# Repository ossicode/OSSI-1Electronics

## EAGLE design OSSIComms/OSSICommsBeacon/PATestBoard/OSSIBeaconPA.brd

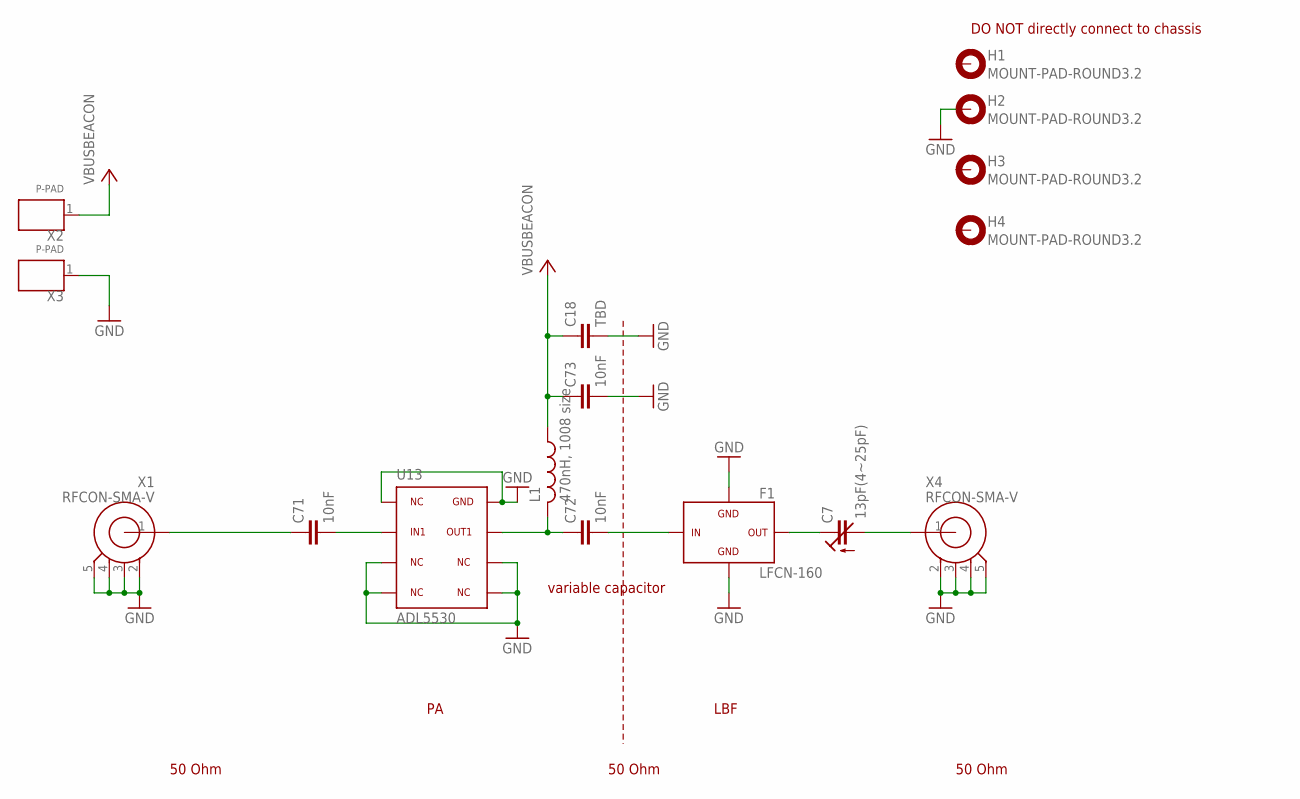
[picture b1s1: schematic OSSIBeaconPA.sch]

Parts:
C7: 13pF(4~25pF); TZB4Z250BA10R00
C18: TBD; C0603(1608)
C71, C72, C73: 10nF; C0603(1608)
F1: LFCN-160; LFCN
H1, H2, H3, H4: MOUNT-PAD-ROUND3.2; 3.2-PAD-ROUND
L1: 470nH, 1008 size; L1008(2520)
U13: ADL5530; LFCSP8_CP
X1, X4: RFCON-SMA-V; SMA-V
X2, X3: P-PAD

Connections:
GND: C18.2, C73.2, F1.2, F1.4, H2.B3,2, U13.1, U13.3, U13.4, U13.5, U13.6, U13.8, X1.2, X1.3, X1.4, X1.5, X3.1, X4.2, X4.3, X4.4, X4.5
unnamed: C71.1, X1.1
unnamed: C7.+ (E), F1.3
unnamed: C7.- (A), X4.1
unnamed: C72.2, F1.1
unnamed: C72.1, L1.P$2 (2), U13.7
unnamed: C71.2, U13.2
VBUSBEACON: C18.1, C73.1, L1.P$1 (1), X2.1

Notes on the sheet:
50 Ohm
LBF
variable capacitor
DO NOT directly connect to chassis

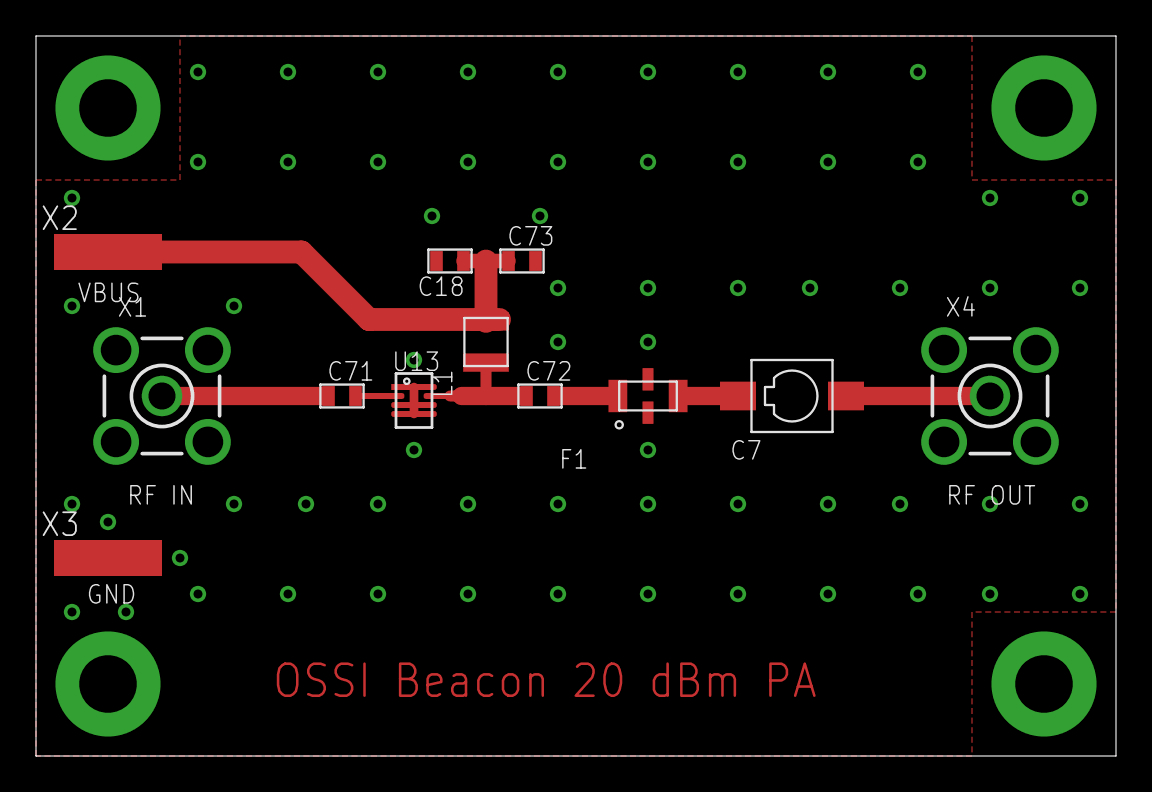
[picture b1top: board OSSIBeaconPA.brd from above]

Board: 2 copper layers, 60.0 x 40.0 mm, 16 parts (0 on the bottom side), 8 nets.

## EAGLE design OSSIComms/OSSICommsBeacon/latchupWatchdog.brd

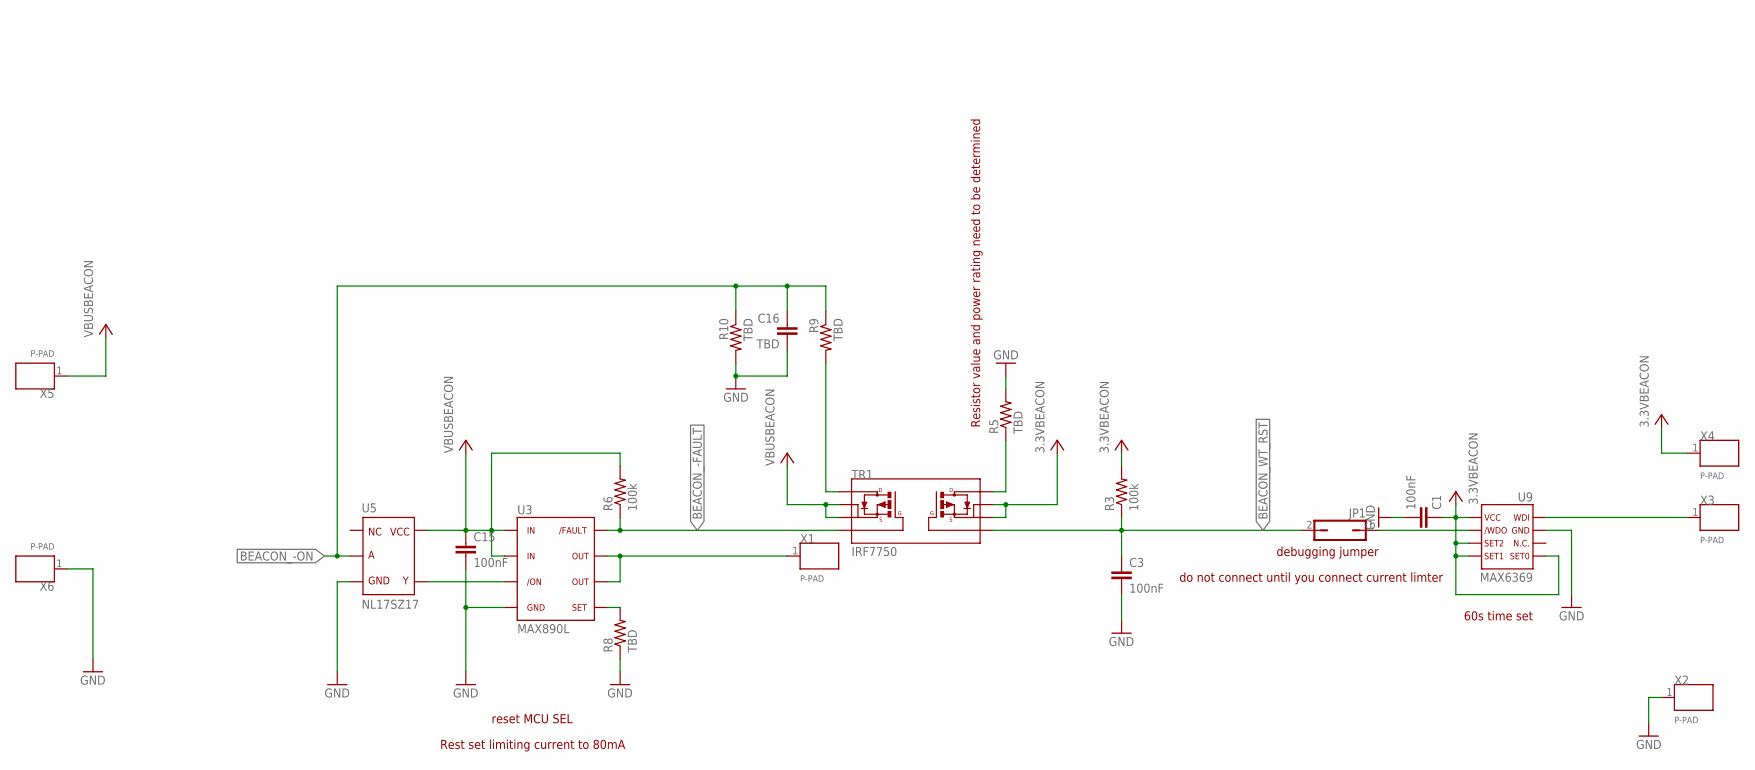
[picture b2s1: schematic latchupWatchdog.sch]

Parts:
C1, C3, C15: 100nF; C0603(1608)
C16: TBD; C0603(1608)
JP1: JP1Q; JP1
R3, R6: 100k; R0603(1608)
R5: TBD; R0805(2012)
R8, R9, R10: TBD; R0603(1608)
TR1: IRF7750; TSSOP-8
U3: MAX890L; SO8
U5: NL17SZ17; SOT-553
U9: MAX6369; SOT23-8
X1, X2, X3, X4, X5, X6: P-PAD

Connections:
3.3VBEACON: C1.1, R3.2, TR1.6, TR1.7, U9.4, U9.5, U9.6, U9.8, X4.1
BEACON_-FAULT: R6.1, TR1.4, U3.8
BEACON_-ON: C16.1, R9.1, R10.1, U5.2
BEACON_WT_RST: C3.1, JP1.2, R3.1, TR1.5
GND: C1.2, C3.2, C15.2, C16.2, R5.2, R8.1, R10.2, U3.4, U5.3, U9.2, X2.1, X6.1
unnamed: JP1.1, U9.7
unnamed: U9.1, X3.1
unnamed: R5.1, TR1.8
unnamed: U3.6, U3.7, X1.1
unnamed: R8.2, U3.5
unnamed: U3.3, U5.4
unnamed: R9.2, TR1.1
VBUSBEACON: C15.1, R6.2, TR1.2, TR1.3, U3.1, U3.2, U5.5, X5.1

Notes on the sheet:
60s time set
Resistor value and power rating need to be determined
debugging jumper
do not connect until you connect current limter
reset MCU SEL
Rest set limiting current to 80mA

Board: 2 copper layers, 21 parts (0 on the bottom side), 13 nets, no tracks yet.

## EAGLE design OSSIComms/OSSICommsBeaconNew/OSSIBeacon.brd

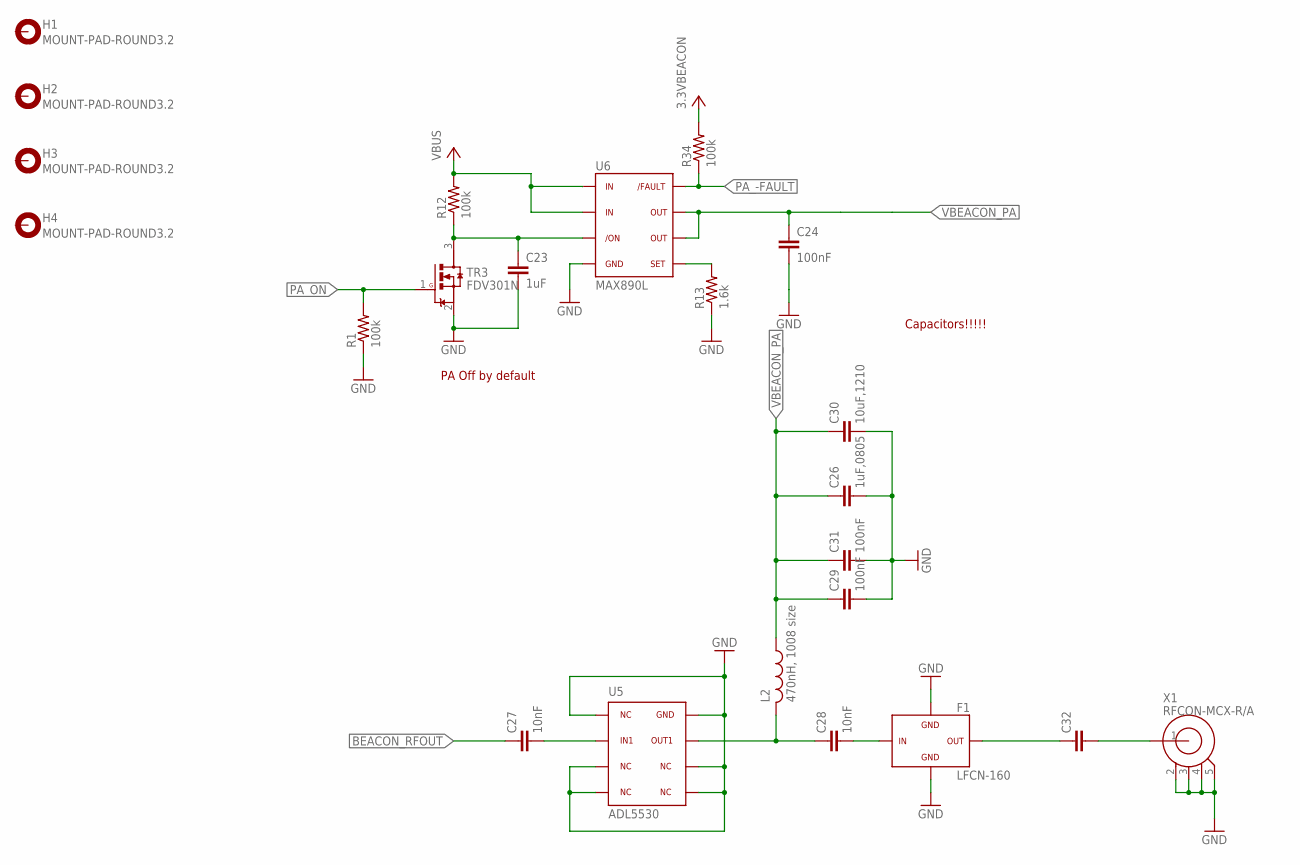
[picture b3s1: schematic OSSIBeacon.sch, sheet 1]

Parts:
C23: 1uF; C0603(1608)
C24, C29, C31: 100nF; C0603(1608)
C26: 1uF,0805; C0805(2012)
C27, C28: 10nF; C0603(1608)
C30: 10uF,1210; C1210-GCM32
C32: C0603(1608)
F1: LFCN-160; LFCN
H1, H2, H3, H4: MOUNT-PAD-ROUND3.2; 3.2-PAD-ROUND
L2: 470nH, 1008 size; L1008(2520)
R1, R12, R34: 100k; R0603(1608)
R13: 1.6k; R0603(1608)
TR3: FDV301N; SOT23
U5: ADL5530; LFCSP8_CP
U6: MAX890L; SO8
X1: RFCON-MCX-R/A; MCX-R/A

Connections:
3.3VBEACON: R34.2; also elsewhere on the board
BEACON_RFOUT: C27.1; also elsewhere on the board
GND: C23.2, C24.2, C26.2, C29.2, C30.P$2 (2), C31.2, F1.2, F1.4, R1.1, R13.1, TR3.2 (S), U5.1, U5.3, U5.4, U5.5, U5.6, U5.8, U6.4, X1.2, X1.3, X1.4, X1.5; also elsewhere on the board
unnamed: C23.1, R12.1, TR3.3 (D), U6.3
unnamed: R13.2, U6.5
unnamed: C27.2, U5.2
unnamed: C28.1, L2.P$2 (2), U5.7
unnamed: C28.2, F1.1
unnamed: C32.1, F1.3
unnamed: C32.2, X1.1
PA_-FAULT: R34.1, U6.8; also elsewhere on the board
PA_ON: R1.2, TR3.1 (G); also elsewhere on the board
VBEACON_PA: C24.1, C26.1, C29.1, C30.P$1 (1), C31.1, L2.P$1 (1), U6.6, U6.7
VBUS: R12.2, U6.1, U6.2; also elsewhere on the board

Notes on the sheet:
Capacitors!!!!!
PA Off by default

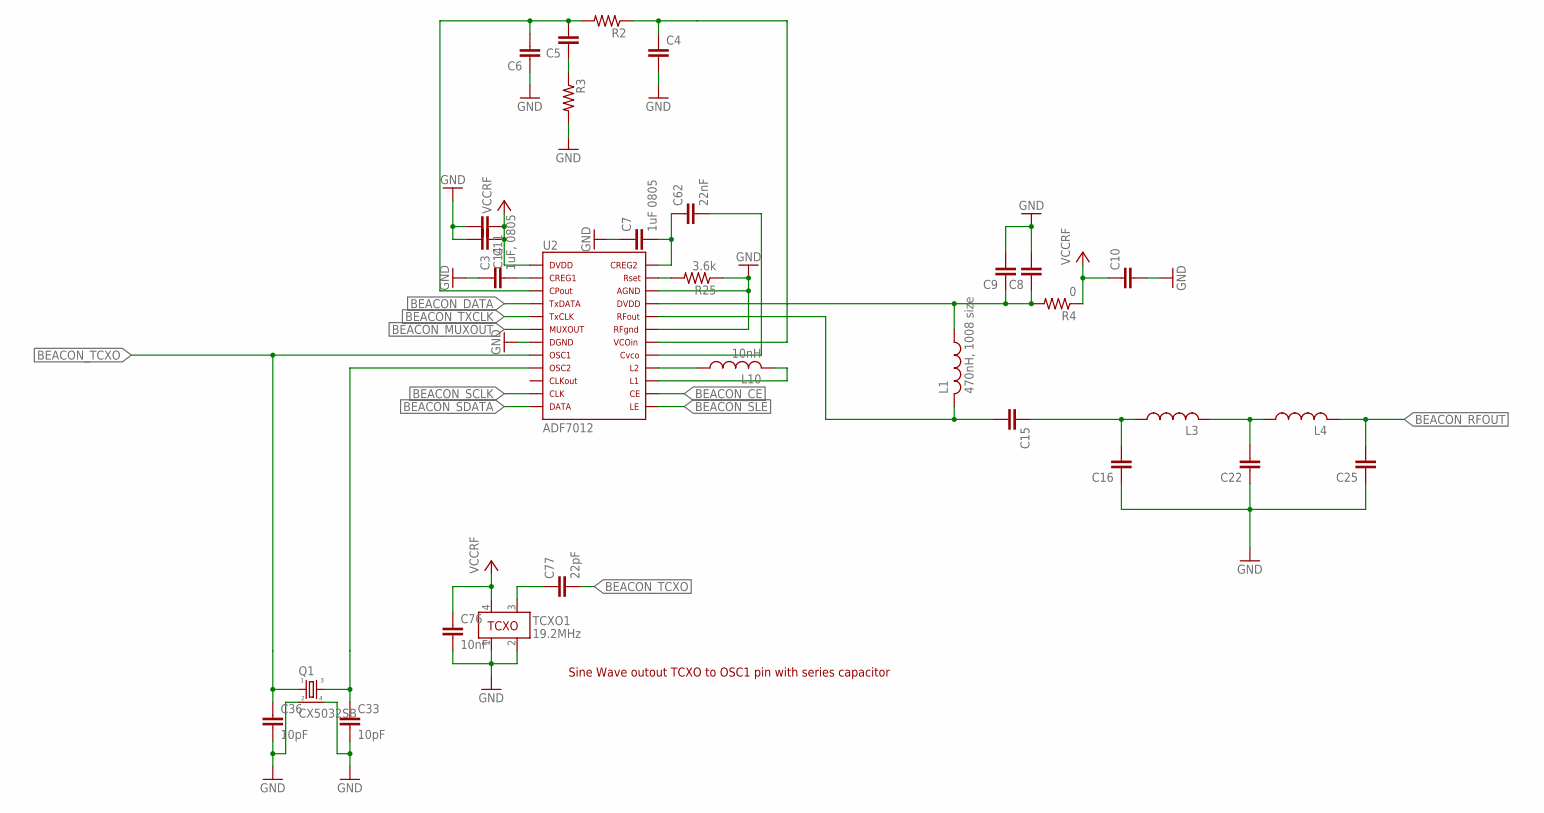
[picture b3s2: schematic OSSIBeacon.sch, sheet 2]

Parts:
C3: 1uF, 0805; C0805(2012)
C4, C5, C6, C8, C9, C10, C11, C14, C15, C16, C22, C25: C0603(1608)
C7: 1uF 0805; C0805(2012)
C33, C36: 10pF; C0603(1608)
C62: 22nF; C0603(1608)
C76: 10nF; C0603(1608)
C77: 22pF; C0603(1608)
L1: 470nH, 1008 size; L1008(2520)
L3, L4: L0603(1608)
L10: 10nH; L0603(1608)
Q1: CX5032SB; CX5032
R2, R3: R0603(1608)
R4: 0; R0603(1608)
R25: 3.6k; R0603(1608)
TCXO1: 19.2MHz; TCXO_M532
U2: ADF7012; TSSOP24

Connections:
BEACON_CE: U2.14 (CE); also elsewhere on the board
BEACON_DATA: U2.4 (TXDATA); also elsewhere on the board
BEACON_MUXOUT: U2.6 (MUXOUT); also elsewhere on the board
BEACON_RFOUT: C25.2, L4.2; also elsewhere on the board
BEACON_SCLK: U2.11 (CLK); also elsewhere on the board
BEACON_SDATA: U2.12 (DATA); also elsewhere on the board
BEACON_SLE: U2.13 (LE); also elsewhere on the board
BEACON_TCXO: C36.1, C77.2, Q1.1, U2.8 (OSC1)
BEACON_TXCLK: U2.5 (TXCLK); also elsewhere on the board
GND: C3.1, C4.2, C6.1, C7.1, C8.2, C9.2, C10.2, C11.2, C14.2, C16.1, C22.1, C25.1, C33.2, C36.2, C76.2, Q1.2, Q1.4, R3.2, R25.1, TCXO1.1, TCXO1.2, U2.7 (DGND), U2.19 (RFGND), U2.22 (AGND); also elsewhere on the board
unnamed: L10.1, U2.16 (L2)
unnamed: L10.2, U2.15 (L1)
unnamed: C7.2, C62.1, U2.24 (CREG2)
unnamed: C62.2, U2.17 (CVCO)
unnamed: R25.2, U2.23 (RSET)
unnamed: C5.1, R3.1
unnamed: C15.2, L1.P$2 (2), U2.20 (RFOUT)
unnamed: C4.1, R2.1, U2.18 (VCOIN)
unnamed: C3.2, U2.2 (CREG1)
unnamed: C5.2, C6.2, R2.2, U2.3 (CPOUT)
unnamed: C8.1, C9.1, L1.P$1 (1), R4.2, U2.21 (DVDD_2)
unnamed: C15.1, C16.2, L3.1
unnamed: C22.2, L3.2, L4.1
unnamed: C33.1, Q1.3, U2.9 (OSC2)
unnamed: C77.1, TCXO1.3
VCCRF: C10.1, C11.1, C14.1, C76.1, R4.1, TCXO1.4, U2.1 (DVDD_1); also elsewhere on the board

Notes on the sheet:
Sine Wave outout TCXO to OSC1 pin with series capacitor

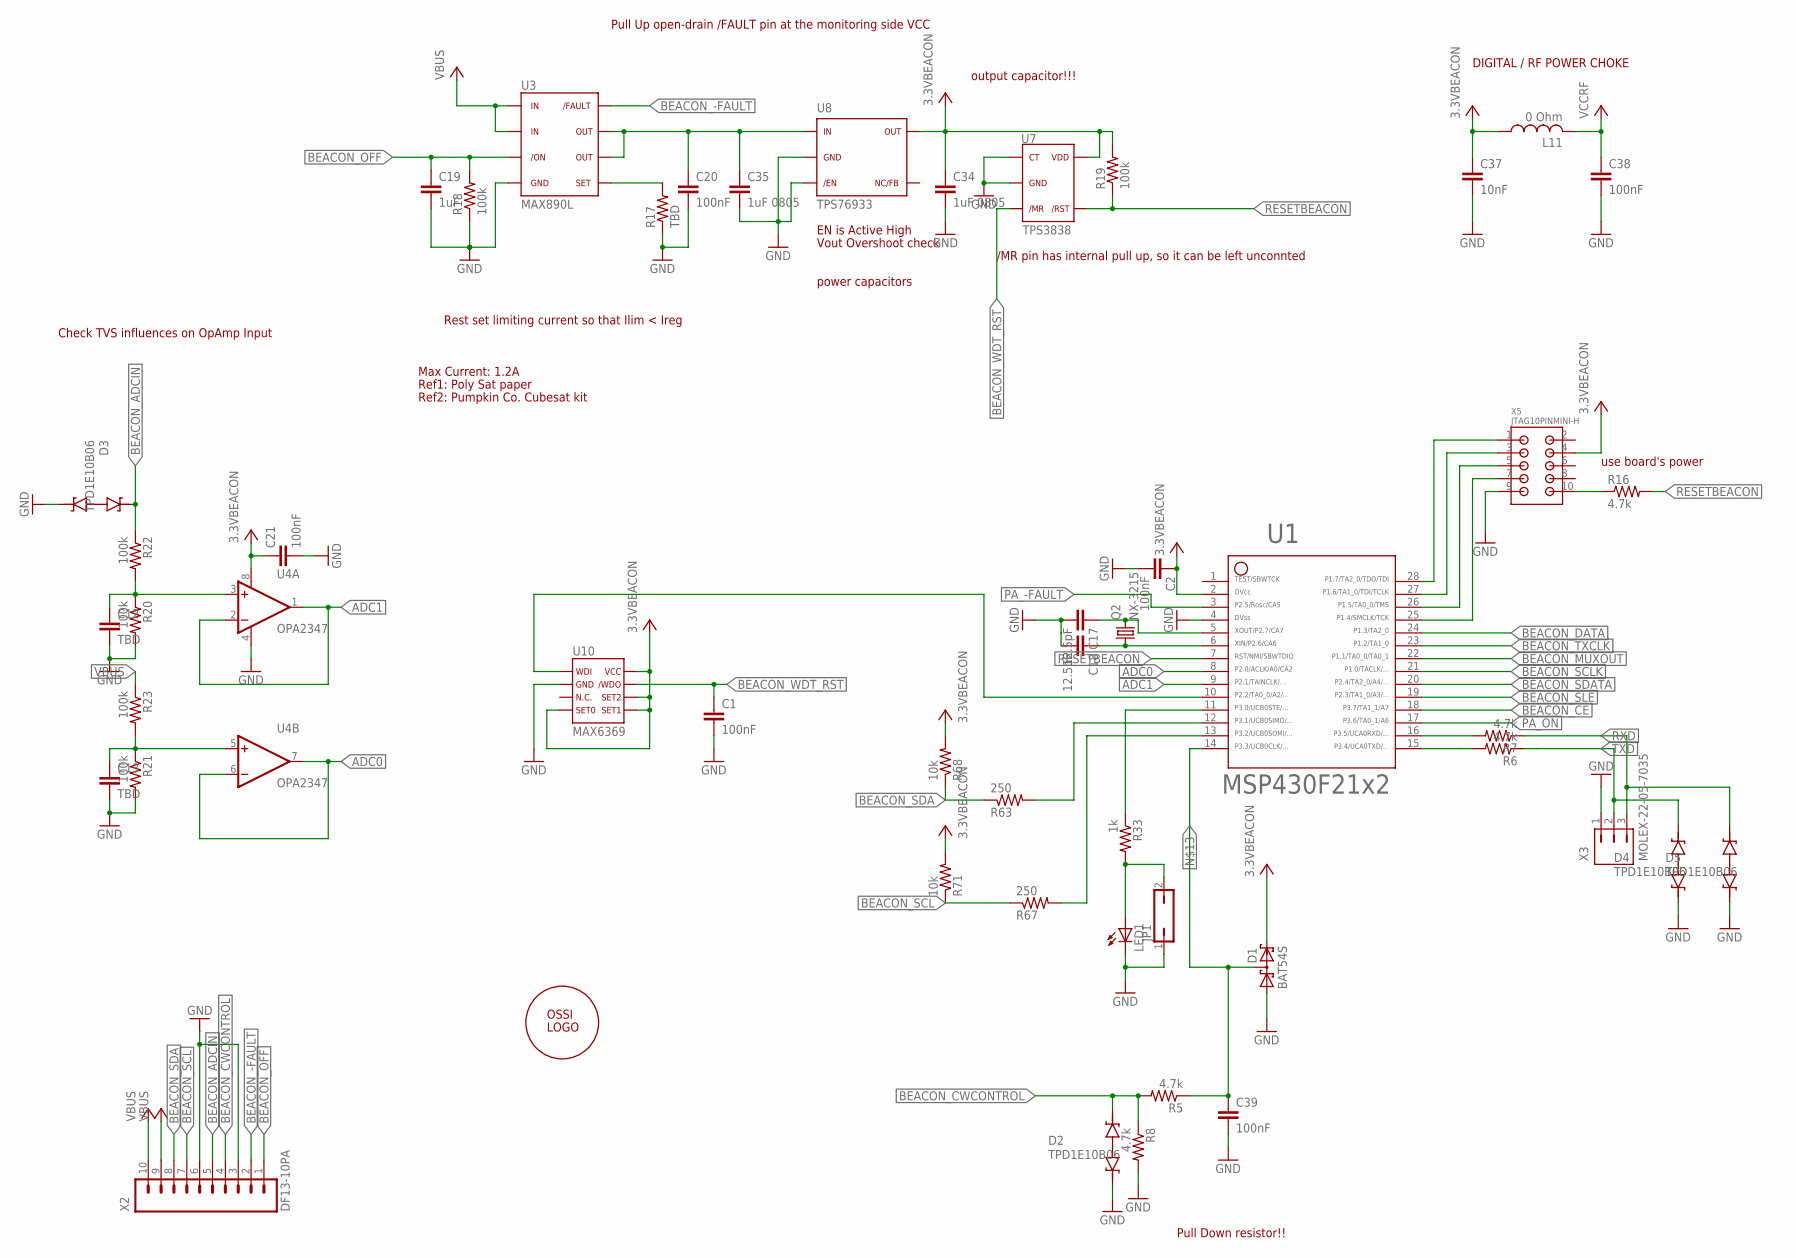
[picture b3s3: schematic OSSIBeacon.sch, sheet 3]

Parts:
C1, C2, C20, C21, C38, C39: 100nF; C0603(1608)
C12, C13: TBD; C0603(1608)
C17, C18: 12.5pF; C0603(1608)
C19: 1uF; C0603(1608)
C34, C35: 1uF 0805; C0805(2012)
C37: 10nF; C0603(1608)
D1: BAT54S; SOT23
D2, D3, D4, D5: TPD1E10B06; X2SON
JP1: JP1Q; JP1
L11: 0 Ohm; L0805(2012)
LED1: LED0603; LED-0603
Q2: NX-3215
R5, R6, R7, R8, R16: 4.7k; R0603(1608)
R17: TBD; R0603(1608)
R18, R19, R20, R21, R22, R23: 100k; R0603(1608)
R33: 1k; R0603(1608)
R63, R67: 250; R0603(1608)
R68, R71: 10k; R0603(1608)
U1: MSP430F2132; PW28
U3: MAX890L; SO8
U4: OPA2347; SOT23-8DCN
U7: TPS3838; SOT23-5DBV
U8: TPS76933; SOT23-5DBV
U10: MAX6369; SOT23-8
U$1: OSSILOGORECT; OSSILOGORECT1005
X2: DF13-10PA; DF13A-10P
X3: MOLEX-22-05-7035; 22-05-7035
X5: JTAG10PINMINI-H; M50-3200545

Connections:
3.3VBEACON: C2.1, C21.1, C34.1, C37.1, D1.2 (C2), L11.1, R19.2, R68.2, R71.2, U1.2, U4.8 (V+), U7.5, U8.5, U10.4, U10.5, U10.6, U10.8, X5.4; also elsewhere on the board
ADC0: U1.8, U4.6 (-IN), U4.7 (OUT)
ADC1: U1.9, U4.1 (OUT), U4.2 (-IN)
BEACON_-FAULT: U3.8, X2.2
BEACON_ADCIN: D3.1, R22.1, X2.5
BEACON_CE: U1.18; also elsewhere on the board
BEACON_CWCONTROL: D2.1, R5.2, R8.1, X2.4
BEACON_DATA: U1.24; also elsewhere on the board
BEACON_MUXOUT: U1.22; also elsewhere on the board
BEACON_OFF: C19.1, R18.2, U3.3, X2.1
BEACON_SCL: R67.1, R71.1, X2.7
BEACON_SCLK: U1.21; also elsewhere on the board
BEACON_SDA: R63.1, R68.1, X2.8
BEACON_SDATA: U1.20; also elsewhere on the board
BEACON_SLE: U1.19; also elsewhere on the board
BEACON_TXCLK: U1.23; also elsewhere on the board
BEACON_WDT_RST: C1.1, U7.3, U10.7
GND: C1.2, C2.2, C12.2, C13.2, C17.2, C18.2, C19.2, C20.2, C21.2, C34.2, C35.2, C37.2, C38.2, C39.2, D1.1 (A1), D2.2, D3.2, D4.2, D5.2, JP1.1, LED1.C, R8.2, R17.1, R18.1, R20.2, R21.2, U1.4, U3.4, U4.4 (V-), U7.1, U7.2, U8.2, U8.3, U10.2, X2.3, X2.6, X3.1, X5.9; also elsewhere on the board
unnamed: R33.1, U1.11
unnamed: U1.27, X5.3
unnamed: U1.26, X5.5
unnamed: U1.25, X5.7
unnamed: C17.1, Q2.2, U1.5
unnamed: C18.1, Q2.1, U1.6
unnamed: JP1.2, LED1.A, R33.2
unnamed: U1.28, X5.1
unnamed: R63.2, U1.12
unnamed: R67.2, U1.13
unnamed: R7.2, U1.16
unnamed: U1.10, U10.1
unnamed: C39.1, D1.3 (C1A2), R5.1, U1.14
unnamed: C13.1, R21.1, R23.2, U4.5 (+IN)
unnamed: R16.1, X5.10
unnamed: R17.2, U3.5
unnamed: C12.1, R20.1, R22.2, U4.3 (+IN)
unnamed: R6.2, U1.15
unnamed: C20.1, C35.1, U3.6, U3.7, U8.1
PA_-FAULT: U1.3; also elsewhere on the board
PA_ON: U1.17; also elsewhere on the board
RESETBEACON: R16.2, R19.1, U1.7, U7.4
RXD: D5.1, R7.1, X3.3
TXD: D4.1, R6.1, X3.2
VBUS: R23.1, U3.1, U3.2, X2.9, X2.10; also elsewhere on the board
VCCRF: C38.1, L11.2; also elsewhere on the board

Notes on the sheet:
Rest set limiting current so that Ilim < Ireg
Pull Up open-drain /FAULT pin at the monitoring side VCC
Max Current: 1.2A
Ref1: Poly Sat paper
Ref2: Pumpkin Co. Cubesat kit
EN is Active High
/MR pin has internal pull up, so it can be left unconnted
Vout Overshoot check
power capacitors
output capacitor!!!
use board's power
DIGITAL / RF POWER CHOKE
Pull Down resistor!!
Check TVS influences on OpAmp Input

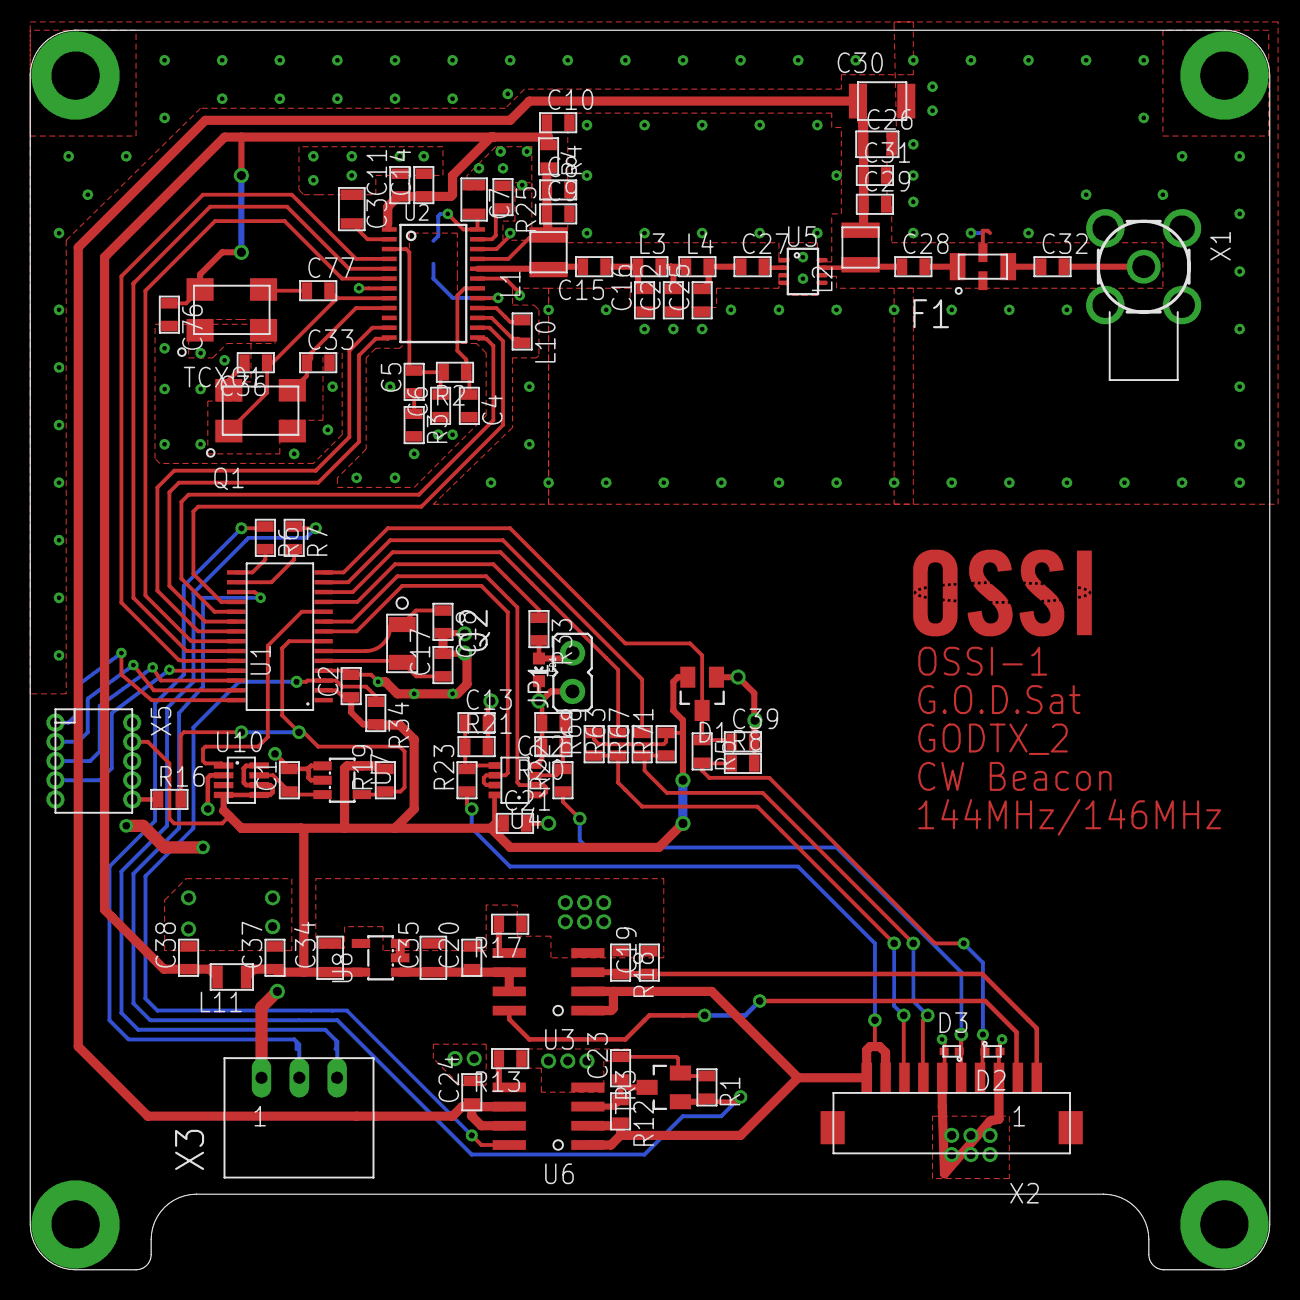
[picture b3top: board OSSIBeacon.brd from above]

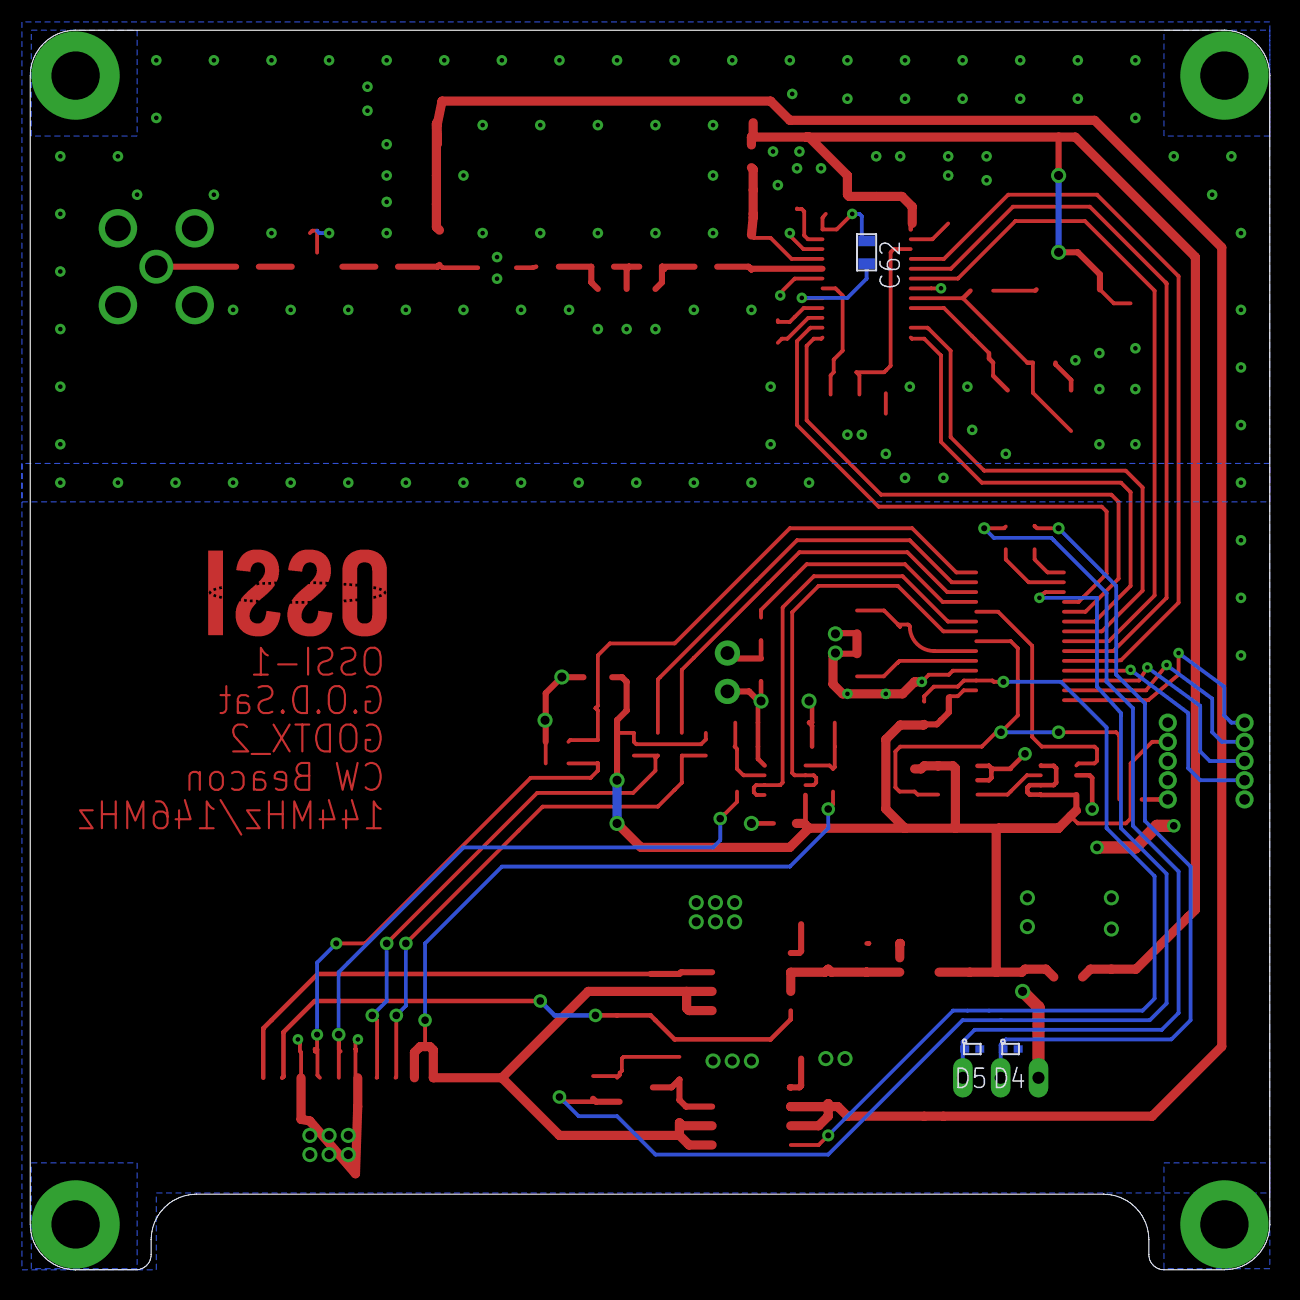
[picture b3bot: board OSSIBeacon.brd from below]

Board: 2 copper layers, 82.0 x 82.0 mm, 103 parts (3 on the bottom side), 69 nets.

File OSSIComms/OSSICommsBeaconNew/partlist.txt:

Partlist

Exported from OSSIBeacon.sch at 2012-12-10 ¿ÀÈÄ 5:49:18

EAGLE Version 6.1.0 Copyright (c) 1988-2012 CadSoft

Assembly variant: 

Part     Value              Device             Package       Library  Sheet

C1       100nF              C0603(1608)        C0603(1608)   OSSI     3
C2       100nF              C0603(1608)        C0603(1608)   OSSI     3
C3       1uF, 0805          C0805(2012)        C0805(2012)   OSSI     2
C4                          C0603(1608)        C0603(1608)   OSSI     2
C5                          C0603(1608)        C0603(1608)   OSSI     2
C6                          C0603(1608)        C0603(1608)   OSSI     2
C7       1uF 0805           C0805(2012)        C0805(2012)   OSSI     2
C8                          C0603(1608)        C0603(1608)   OSSI     2
C9                          C0603(1608)        C0603(1608)   OSSI     2
C10                         C0603(1608)        C0603(1608)   OSSI     2
C11                         C0603(1608)        C0603(1608)   OSSI     2
C12      TBD                C0603(1608)        C0603(1608)   OSSI     3
C13      TBD                C0603(1608)        C0603(1608)   OSSI     3
C14                         C0603(1608)        C0603(1608)   OSSI     2
C15                         C0603(1608)        C0603(1608)   OSSI     2
C16                         C0603(1608)        C0603(1608)   OSSI     2
C17      12.5pF             C0603(1608)        C0603(1608)   OSSI     3
C18      12.5pF             C0603(1608)        C0603(1608)   OSSI     3
C19      1uF                C0603(1608)        C0603(1608)   OSSI     3
C20      100nF              C0603(1608)        C0603(1608)   OSSI     3
C21      100nF              C0603(1608)        C0603(1608)   OSSI     3
C22                         C0603(1608)        C0603(1608)   OSSI     2
C23      1uF                C0603(1608)        C0603(1608)   OSSI     1
C24      100nF              C0603(1608)        C0603(1608)   OSSI     1
C25                         C0603(1608)        C0603(1608)   OSSI     2
C26      1uF,0805           C0805(2012)        C0805(2012)   OSSI     1
C27      10nF               C0603(1608)        C0603(1608)   OSSI     1
C28      10nF               C0603(1608)        C0603(1608)   OSSI     1
C29      100nF              C0603(1608)        C0603(1608)   OSSI     1
C30      10uF,1210          C1210(3225)-GCM32  C1210-GCM32   OSSI     1
C31      100nF              C0603(1608)        C0603(1608)   OSSI     1
C32                         C0603(1608)        C0603(1608)   OSSI     1
C33      10pF               C0603(1608)        C0603(1608)   OSSI     2
C34      1uF 0805           C0805(2012)        C0805(2012)   OSSI     3
C35      1uF 0805           C0805(2012)        C0805(2012)   OSSI     3
C36      10pF               C0603(1608)        C0603(1608)   OSSI     2
C37      10nF               C0603(1608)        C0603(1608)   OSSI     3
C38      100nF              C0603(1608)        C0603(1608)   OSSI     3
C39      100nF              C0603(1608)        C0603(1608)   OSSI     3
C62      22nF               C0603(1608)        C0603(1608)   OSSI     2
C76      10nF               C0603(1608)        C0603(1608)   OSSI     2
C77      22pF               C0603(1608)        C0603(1608)   OSSI     2
D1       BAT54S             BAT54S             SOT23         OSSI     3
D2       TPD1E10B06         TPD1E10B06         X2SON         OSSI     3
D3       TPD1E10B06         TPD1E10B06         X2SON         OSSI     3
D4       TPD1E10B06         TPD1E10B06         X2SON         OSSI     3
D5       TPD1E10B06         TPD1E10B06         X2SON         OSSI     3
F1       LFCN-160           LFCN-160           LFCN          OSSI     1
H1       MOUNT-PAD-ROUND3.2 MOUNT-PAD-ROUND3.2 3.2-PAD-ROUND OSSI     1
H2       MOUNT-PAD-ROUND3.2 MOUNT-PAD-ROUND3.2 3.2-PAD-ROUND OSSI     1
H3       MOUNT-PAD-ROUND3.2 MOUNT-PAD-ROUND3.2 3.2-PAD-ROUND OSSI     1
H4       MOUNT-PAD-ROUND3.2 MOUNT-PAD-ROUND3.2 3.2-PAD-ROUND OSSI     1
JP1                         JP1Q               JP1           OSSI     3
L1       470nH, 1008 size   L1008(2502)        L1008(2520)   OSSI     2
L2       470nH, 1008 size   L1008(2502)        L1008(2520)   OSSI     1
L3                          L0603(1608)        L0603(1608)   OSSI     2
L4                          L0603(1608)        L0603(1608)   OSSI     2
L10      10nH               L0603(1608)        L0603(1608)   OSSI     2
L11      0 Ohm              L0805(2012)        L0805(2012)   OSSI     3
LED1                        LED0603            LED-0603      SparkFun 3
Q1       CX5032SB           CX5032SB           CX5032        OSSI     2
Q2       NX-3215            NX-3215            NX-3215       OSSI     3
R1       100k               R0603(1608)        R0603(1608)   OSSI     1
R2                          R0603(1608)        R0603(1608)   OSSI     2
R3                          R0603(1608)        R0603(1608)   OSSI     2
R4       0                  R0603(1608)        R0603(1608)   OSSI     2
R5       4.7k               R0603(1608)        R0603(1608)   OSSI     3
R6       4.7k               R0603(1608)        R0603(1608)   OSSI     3
R7       4.7k               R0603(1608)        R0603(1608)   OSSI     3
R8       4.7k               R0603(1608)        R0603(1608)   OSSI     3
R12      100k               R0603(1608)        R0603(1608)   OSSI     1
R13      1.6k               R0603(1608)        R0603(1608)   OSSI     1
R16      4.7k               R0603(1608)        R0603(1608)   OSSI     3
R17      TBD                R0603(1608)        R0603(1608)   OSSI     3
R18      100k               R0603(1608)        R0603(1608)   OSSI     3
R19      100k               R0603(1608)        R0603(1608)   OSSI     3
R20      100k               R0603(1608)        R0603(1608)   OSSI     3
R21      100k               R0603(1608)        R0603(1608)   OSSI     3
R22      100k               R0603(1608)        R0603(1608)   OSSI     3
R23      100k               R0603(1608)        R0603(1608)   OSSI     3
R25      3.6k               R0603(1608)        R0603(1608)   OSSI     2
R33      1k                 R0603(1608)        R0603(1608)   OSSI     3
R34      100k               R0603(1608)        R0603(1608)   OSSI     1
R63      250                R0603(1608)        R0603(1608)   OSSI     3
R67      250                R0603(1608)        R0603(1608)   OSSI     3
R68      10k                R0603(1608)        R0603(1608)   OSSI     3
R71      10k                R0603(1608)        R0603(1608)   OSSI     3
TCXO1    19.2MHz            TCXO-M532          TCXO_M532     OSSI     2
TR3      FDV301N            FDV301N            SOT23         OSSI     1
U1       MSP430F2132        MSP430F2132        PW28          OSSI     3
U2       ADF7012            ADF7012            TSSOP24       OSSI     2
U3       MAX890L            MAX890L            SO8           OSSI     3
U4       OPA2347            OPA2347            SOT23-8DCN    OSSI     3
U5       ADL5530            ADL5530            LFCSP8_CP     OSSI     1
U6       MAX890L            MAX890L            SO8           OSSI     1
U7       TPS3838            TPS3838            SOT23-5DBV    OSSI     3
U8       TPS76933           TPS76933           SOT23-5DBV    OSSI     3
U10      MAX6369            MAX6369            SOT23-8       OSSI     3
X1       RFCON-MCX-R/A      RFCON-MCX-R/A      MCX-R/A       OSSI     1
X2       DF13-10PA          DF13-10PA          DF13A-10P     OSSI     3
X3       MOLEX-22-05-7035   MOLEX-22-05-7035   22-05-7035    OSSI     3
X5       JTAG10PINMINI-H    JTAG10PINMINI-H    M50-3200545   OSSI     3

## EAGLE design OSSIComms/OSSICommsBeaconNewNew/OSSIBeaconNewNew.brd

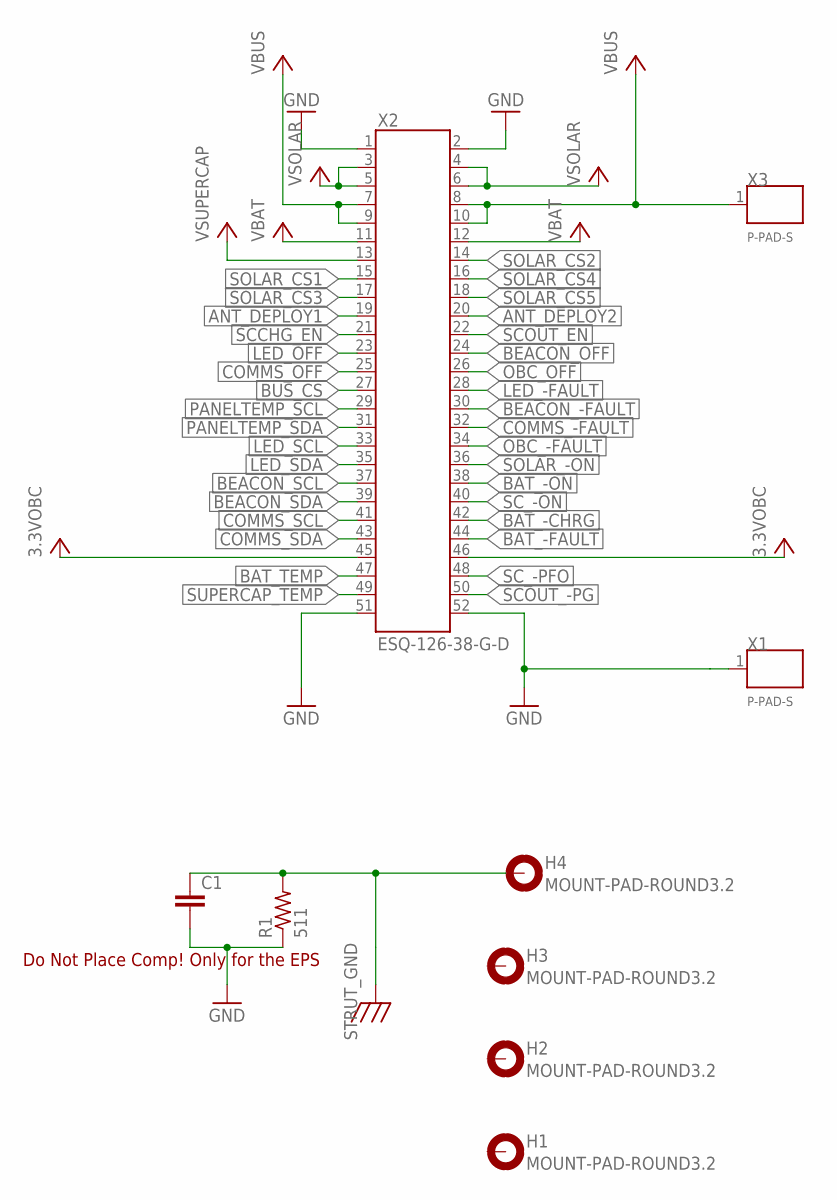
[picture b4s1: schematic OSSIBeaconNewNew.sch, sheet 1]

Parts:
C1: C0805(2012)
H1, H2, H3, H4: MOUNT-PAD-ROUND3.2; 3.2-PAD-ROUND
R1: 511; WSL1206
X1, X3: P-PAD-S
X2: ESQ-126-38-G-D; ESQ-126-XX-X-D

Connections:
3.3VOBC: X2.45, X2.46
ANT_DEPLOY1: X2.19
ANT_DEPLOY2: X2.20
BAT_-CHRG: X2.42
BAT_-FAULT: X2.44
BAT_-ON: X2.38
BAT_TEMP: X2.47
BEACON_-FAULT: X2.30; also elsewhere on the board
BEACON_OFF: X2.24; also elsewhere on the board
BEACON_SCL: X2.37; also elsewhere on the board
BEACON_SDA: X2.39; also elsewhere on the board
BUS_CS: X2.27; also elsewhere on the board
COMMS_-FAULT: X2.32
COMMS_OFF: X2.25
COMMS_SCL: X2.41
COMMS_SDA: X2.43
GND: C1.2, R1.P$1 (1), X1.1, X2.1, X2.2, X2.51, X2.52; also elsewhere on the board
LED_-FAULT: X2.28
LED_OFF: X2.23
LED_SCL: X2.33
LED_SDA: X2.35
OBC_-FAULT: X2.34
OBC_OFF: X2.26
PANELTEMP_SCL: X2.29
PANELTEMP_SDA: X2.31
SCCHG_EN: X2.21
SCOUT_-PG: X2.50
SCOUT_EN: X2.22
SC_-ON: X2.40
SC_-PFO: X2.48
SOLAR_-ON: X2.36
SOLAR_CS1: X2.15
SOLAR_CS2: X2.14
SOLAR_CS3: X2.17
SOLAR_CS4: X2.16
SOLAR_CS5: X2.18
STRUT_GND: C1.1, H4.B3,2, R1.P$2 (2)
SUPERCAP_TEMP: X2.49
VBAT: X2.11, X2.12
VBUS: X2.7, X2.8, X2.9, X2.10, X3.1; also elsewhere on the board
VSOLAR: X2.3, X2.4, X2.5, X2.6
VSUPERCAP: X2.13

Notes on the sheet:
Do Not Place Comp! Only for the EPS

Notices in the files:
parts and their libraries:
SparkFun: Licensing: CC v3.0 Share-Alike You are welcome to use this library for commercial purposes.
